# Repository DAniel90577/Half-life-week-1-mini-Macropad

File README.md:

# Half-life-week-1-mini-Macropad
This is my protect for hack club week 1 where i am designing a customizable Macropad for anything.

| Part | What it's for | Qty | Unit | Total | Vendor |
| --- | --- | --- | --- | --- | --- |
| [Seeed Studio XIAO RP2040 dip (pre soldered)](https://www.seeedstudio.com/Seeed-Studio-XIAO-RP2040-Pre-Soldered-p-6333.html) | micro controller to process the inputs | 1 | $4.99 | $4.99 | [SEEED Studio](https://www.seeedstudio.com/Seeed-Studio-XIAO-RP2040-Pre-Soldered-p-6333.html) |
| [Cherry   MX   Red   Linear   RGB   Switches](https://www.thockking.com/products/cherry-mx-red-rgb-switches?country=US&currency=USD&utm_medium=product_sync&utm_source=google&utm_content=sag_organic&utm_campaign=sag_organic&variant=42102688481496) | the main keys of the macro pad | 1 | $3.45 | $3.45 | [Thock King](https://www.thockking.com/products/cherry-mx-red-rgb-switches?country=US&currency=USD&utm_medium=product_sync&utm_source=google&utm_content=sag_organic&utm_campaign=sag_organic&variant=42102688481496) |
| **Parts subtotal** | — | — | — | **$8.44** | — |
| **Tax & shipping** | — | — | — | **$0.00** | — |
| **Total** | — | — | — | **$8.44** | — |

$21.56 left of the tier's funding.

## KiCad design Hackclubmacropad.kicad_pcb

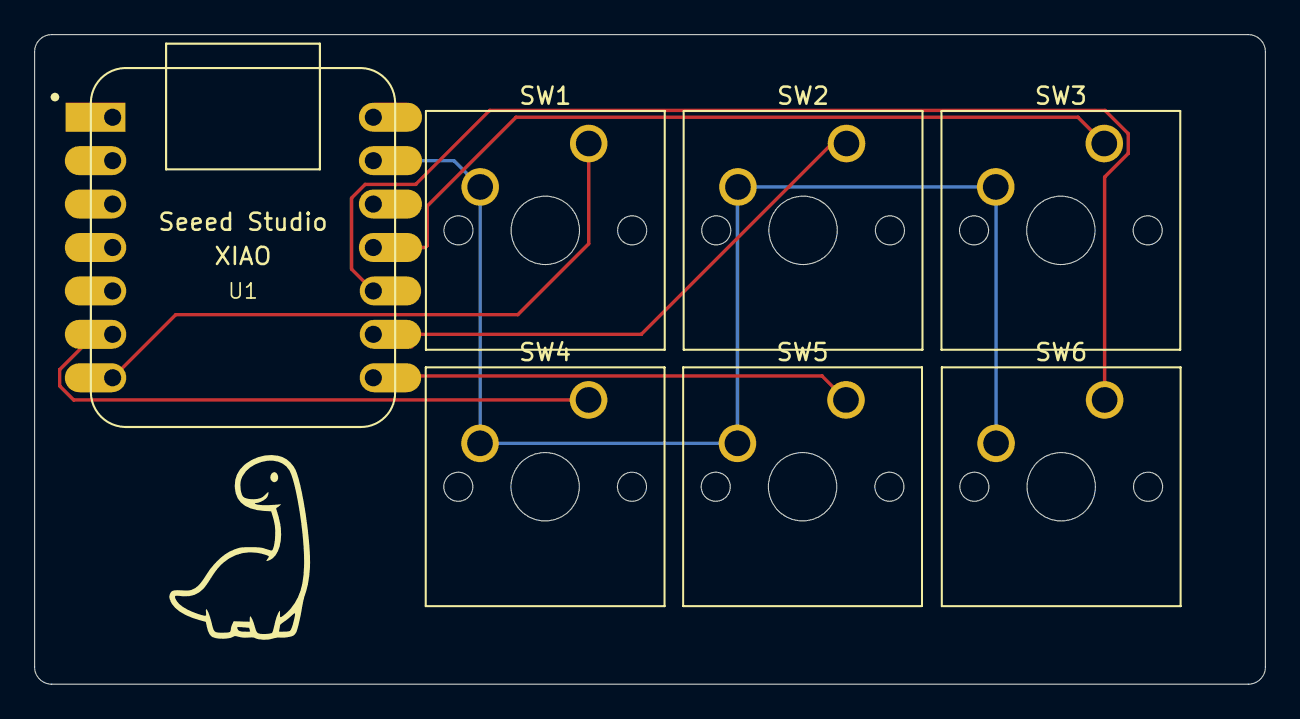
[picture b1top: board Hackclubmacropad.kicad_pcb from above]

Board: 2 copper layers, 72.0 x 38.0 mm, 7 parts (0 on the bottom side), 7 nets.

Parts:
SW1, SW2, SW3, SW4, SW5, SW6: SW_Push; SW_Cherry_MX_1.00u_PCB
U1: XIAO-RP2040-DIP; XIAO-Generic-Hybrid-14P-2.54-21X17.8MM

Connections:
GND: SW1.2, SW2.2, SW3.2, SW4.2, SW5.2, SW6.2, U1.13 (GND)
unnamed: SW1.1, U1.7 (GPIO0/TX)
unnamed: SW5.1, U1.8 (GPIO1/RX)
unnamed: SW2.1, U1.9 (GPIO2/SCK)
unnamed: SW3.1, U1.11 (GPIO3/MOSI)
unnamed: SW6.1, U1.10 (GPIO4/MISO)
unnamed: SW4.1, U1.6 (GPIO7/SCL)
